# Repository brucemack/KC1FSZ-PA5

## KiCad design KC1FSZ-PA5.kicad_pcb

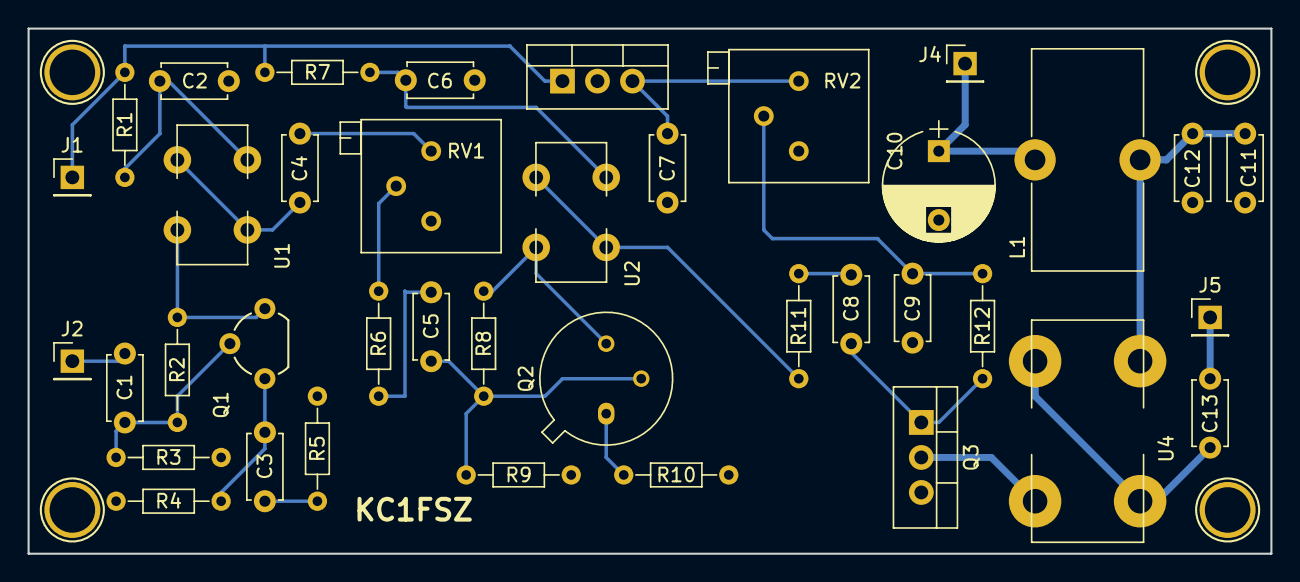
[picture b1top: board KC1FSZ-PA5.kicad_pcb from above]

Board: 2 copper layers, 90.2 x 38.1 mm, 40 parts (0 on the bottom side), 26 nets.

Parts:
C1, C2, C4, C5, C6, C8, C9, C11, C12, C13: C; C_Disc_D4.7mm_W2.5mm_P5.00mm
C3, C7: 0.1u; C_Disc_D4.7mm_W2.5mm_P5.00mm
C10: CP; CP_Radial_D8.0mm_P5.00mm
J1, J2, J4, J5: Conn_01x01; Pin_Header_Straight_1x01_Pitch2.54mm
J3: Conn_01x01; 1pin
L1: L; L_Toroid_Vertical_L16.0mm_W8.0mm_P7.62mm
Q1: Q_NPN_EBC; TO-92_Molded_Wide
Q2: Q_NPN_EBC; TO-39-3
Q3: IRF510; TO-220_Vertical
R1, R6, R7, R8, R9, R10, R12: R; R_Axial_DIN0204_L3.6mm_D1.6mm_P7.62mm_Horizontal
R2: 10k; R_Axial_DIN0204_L3.6mm_D1.6mm_P7.62mm_Horizontal
R3: 470; R_Axial_DIN0204_L3.6mm_D1.6mm_P7.62mm_Horizontal
R4: 100; R_Axial_DIN0204_L3.6mm_D1.6mm_P7.62mm_Horizontal
R5: 10; R_Axial_DIN0204_L3.6mm_D1.6mm_P7.62mm_Horizontal
R11: 0; R_Axial_DIN0204_L3.6mm_D1.6mm_P7.62mm_Horizontal
RV1, RV2: POT; Potentiometer_Trimmer_Bourns_3299P
U1, U2: BifilarTransformer; BifilarTransformer_T37_Vertical
U3: LM7805_TO220; TO-220_Vertical
U4: BifilarTransformer; BifilarTransformer_T50_Vertical

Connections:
GND: C2.2, C6.2, C7.2, C9.2, C10.2, C11.2, C12.2, J3.1, Q3.3, R3.2, R4.2, R5.2, R9.2, R10.2, RV1.3, RV2.3, U3.2
unnamed: C1.1, Q1.2, R2.2, R3.1
unnamed: C1.2, J2.1
unnamed: C2.1, R1.1, U1.1
unnamed: C3.1, R5.1
unnamed: C3.2, Q1.1, R4.1
unnamed: C4.1, RV1.1
unnamed: C4.2, U1.2, U1.3
unnamed: C5.1, Q2.2, R8.2, R9.1
unnamed: C5.2, R6.1
unnamed: C6.1, R7.1, U2.1
unnamed: C7.1, RV2.1, U3.3
unnamed: C8.1, Q3.1, R12.2
unnamed: C8.2, R11.2
unnamed: C9.1, R12.1, RV2.2
unnamed: C10.1, J4.1, L1.1
unnamed: C11.1, C12.1, L1.2, U4.1
unnamed: C13.1, J5.1
unnamed: C13.2, U4.2, U4.3
unnamed: J1.1, R1.2, R7.2, U3.1
unnamed: Q1.3, R2.1, U1.4
unnamed: Q2.1, R10.1
unnamed: Q2.3, R8.1, U2.4
unnamed: Q3.2, U4.4
unnamed: R6.2, RV1.2
unnamed: R11.1, U2.2, U2.3
